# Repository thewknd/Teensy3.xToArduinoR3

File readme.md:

## Teensy 3.0 to Arduino R3 breakout

## Features
- Arduino R3 Shield compatible header
- All Teensy 3.0 pins accessible 
- Battery holder for the RTC
- micro SD card holder
- Reset/Program Button
- I2C pullup resistors
- external power supply
- battery charger circuit
- two dc dc converter (CJ1117)
- XBee (pro) compatible socket
- common nRF24L01(1) module pin header
- USB to Serial converter (FT232RL) attached to Teensy Serial3
- series resistors for all arduino R3 pins
- most parts are from Seeedstudios (new) OPLV1 (for more information: http://www.seeedstudio.com/wiki/Open_parts_library)

top

bottom

## License
Except where otherwise noted, this work is licensed under 

http://creativecommons.org/licenses/by-sa/3.0/

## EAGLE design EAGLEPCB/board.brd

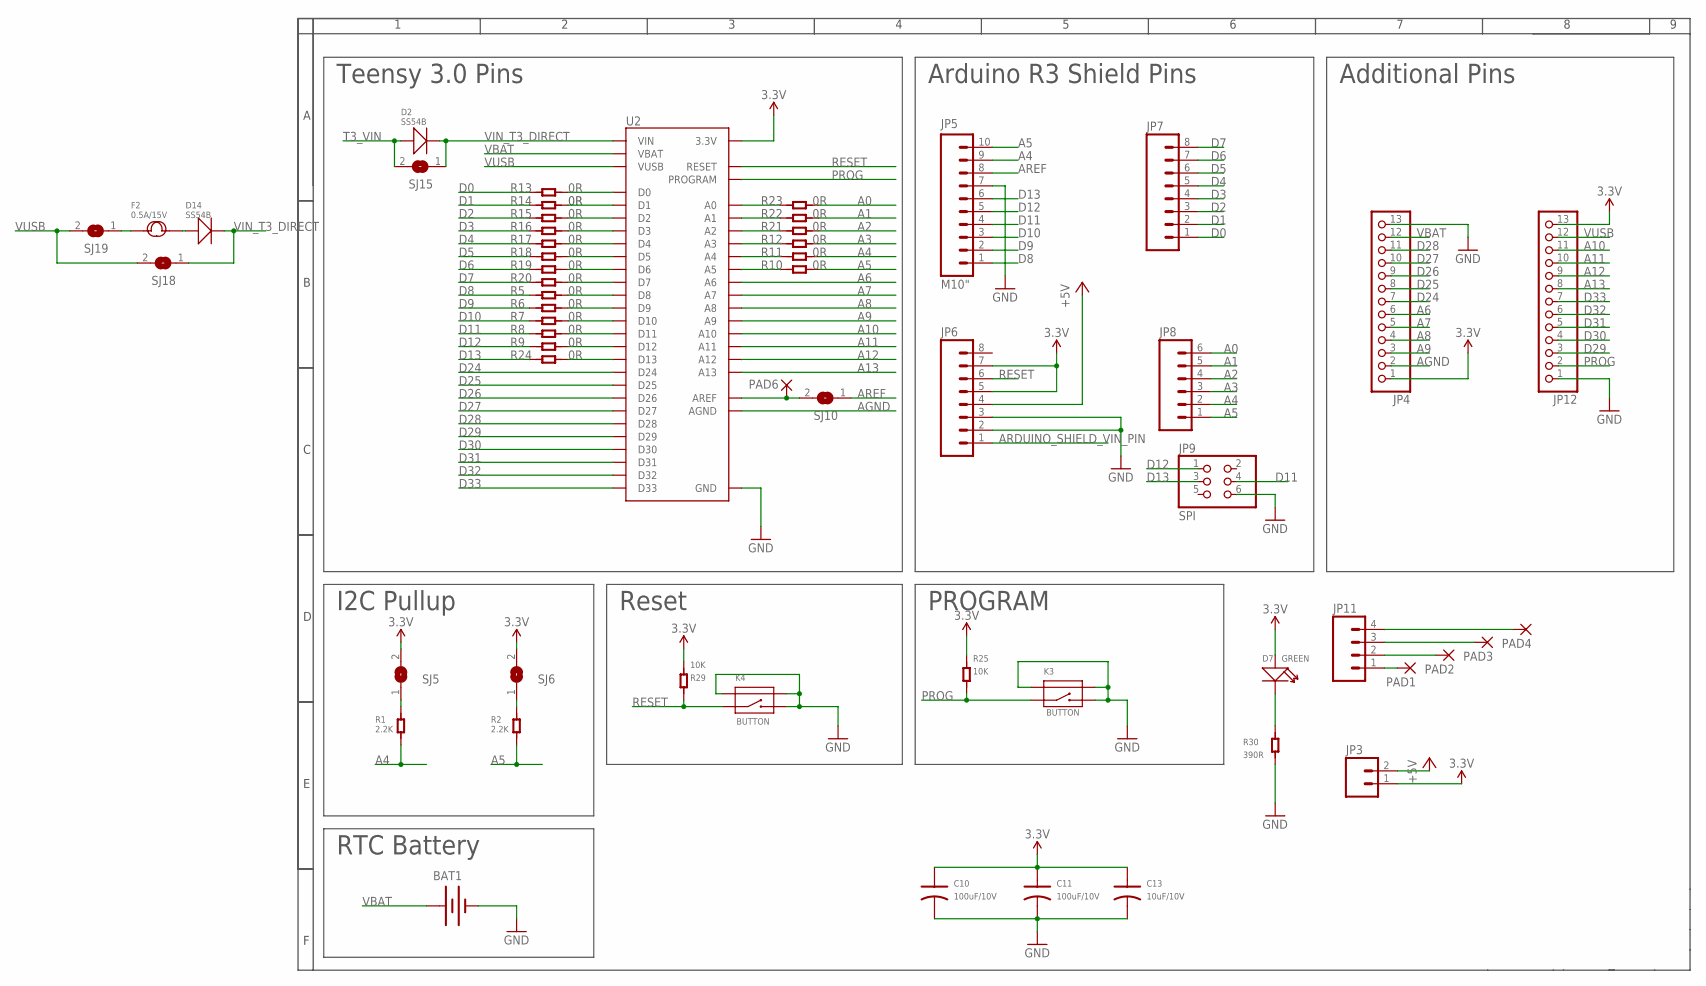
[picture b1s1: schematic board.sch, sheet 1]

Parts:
BAT1: BATTERY12MM; BATTCON_12MM
C10, C11: 100uF/10V; AVX-C
C13: 10uF/10V; AVX-B
D2, D14: SS54B; SMB
D7: GREEN; LED0603
F2: 0.5A/15V; F1812
JP3: M02PTH; 1X02
JP4, JP12: PINHD-1X13_BIG; 1X13-BIG
JP5: M10"; 1X10
JP6, JP7: M081X08; 1X08
JP8: M06SIP; 1X06
JP9: SPI; 2X03
JP11: M04PTH; 1X04
K3, K4: BUTTON; 4P-SMD-7.0X3.5X3.5H-90D
PAD1, PAD2, PAD3, PAD4: WIREPADSMD1,27-254; SMD1,27-2,54
PAD6: AREF; SMD1,27-2,54
R1, R2: 2.2K; R0603
R5, R6, R7, R8, R9, R10, R11, R12, R13, R14, R15, R16, R17, R18, R19, R20, R21, R22, R23, R24: 0R; R0603
R25, R29: 10K; R0603
R30: 390R; R0603
SJ5, SJ6, SJ10, SJ15, SJ18, SJ19: JUMPER_2WLARGE; JUMPER_LARGE_2WAY
U2: TEENSY3.0_ALLPINSSILK; TEENSY3.0_ALLPINS/SILK

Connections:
3.3V: C10.+ (1), C11.+ (1), C13.+ (1), D7.+, JP3.1, JP4.1, JP6.5, JP6.7, JP12.13, R25.2, R29.2, SJ5.2, SJ6.2, U2.3V3_A (3.3V), U2.3V3_B (3.3V), U2.3V3_C (3.3V); also elsewhere on the board
+5V: JP3.2, JP6.4; also elsewhere on the board
A0: JP8.6, R23.1
A1: JP8.5, R22.1
A2: JP8.4, R21.1
A3: JP8.3, R12.1
A4: JP5.9, JP8.2, R1.1, R11.1
A5: JP5.10, JP8.1, R2.1, R10.1
A6: JP4.6, U2.A6
A7: JP4.5, U2.A7
A8: JP4.4, U2.A8
A9: JP4.3, U2.A9
A10: JP12.11, U2.A10
A11: JP12.10, U2.A11
A12: JP12.9, U2.A12
A13: JP12.8, U2.A13
AGND: JP4.2, U2.AGND
ARDUINO_SHIELD_VIN_PIN: JP6.1; also elsewhere on the board
AREF: JP5.8, SJ10.1
D0: JP7.1, R13.2; also elsewhere on the board
D1: JP7.2, R14.2; also elsewhere on the board
D2: JP7.3, R15.2; also elsewhere on the board
D3: JP7.4, R16.2
D4: JP7.5, R17.2; also elsewhere on the board
D5: JP7.6, R18.2
D6: JP7.7, R19.2; also elsewhere on the board
D7: JP7.8, R20.2; also elsewhere on the board
D8: JP5.1, R5.2; also elsewhere on the board
D9: JP5.2, R6.2; also elsewhere on the board
D10: JP5.3, R7.2; also elsewhere on the board
D11: JP5.4, JP9.4, R8.2; also elsewhere on the board
D12: JP5.5, JP9.1, R9.2; also elsewhere on the board
D13: JP5.6, JP9.3, R24.2; also elsewhere on the board
D24: JP4.7, U2.D24; also elsewhere on the board
D25: JP4.8, U2.D25; also elsewhere on the board
D26: JP4.9, U2.D26
D27: JP4.10, U2.D27
D28: JP4.11, U2.D28
D29: JP12.3, U2.D29
D30: JP12.4, U2.D30
D31: JP12.5, U2.D31
D32: JP12.6, U2.D32
D33: JP12.7, U2.D33
DIRECT_AREF: PAD6.1, SJ10.2, U2.AREF
GND: BAT1.GND (-), C10.- (2), C11.- (2), C13.- (2), JP4.13, JP5.7, JP6.2, JP6.3, JP9.6, JP12.1, K3.2, K3.S1, K3.S2, K4.2, K4.S1, K4.S2, R30.1, U2.GND_A (GND), U2.GND_B (GND), U2.GND_C (GND); also elsewhere on the board
unnamed: R13.1, U2.D0
unnamed: R14.1, U2.D1
unnamed: R15.1, U2.D2
unnamed: R16.1, U2.D3
unnamed: R17.1, U2.D4
unnamed: R10.2, U2.A5
unnamed: R11.2, U2.A4
unnamed: R12.2, U2.A3
unnamed: R18.1, U2.D5
unnamed: R19.1, U2.D6
unnamed: R20.1, U2.D7
unnamed: R5.1, U2.D8
unnamed: R6.1, U2.D9
unnamed: R7.1, U2.D10
unnamed: R8.1, U2.D11
unnamed: R9.1, U2.D12
unnamed: R21.2, U2.A2
unnamed: R22.2, U2.A1
unnamed: R23.2, U2.A0
unnamed: R24.1, U2.D13
unnamed: R1.2, SJ5.1
unnamed: R2.2, SJ6.1
unnamed: D7.-, R30.2
unnamed: JP11.1, PAD1.1
unnamed: JP11.2, PAD2.1
unnamed: JP11.3, PAD3.1
unnamed: JP11.4, PAD4.1
unnamed: D14.+, F2.2
unnamed: F2.1, SJ19.1
PROG: JP12.2, K3.1, R25.1, U2.PROG (PROGRAM)
RESET: JP6.6, K4.1, R29.1, U2.RESET; also elsewhere on the board
T3_VIN: D2.+, SJ15.2; also elsewhere on the board
VBAT: BAT1.PWR@1 (+), JP4.12, U2.VBAT
VIN_T3_DIRECT: D2.-, D14.-, SJ15.1, SJ18.1, U2.VIN
VUSB: JP12.12, SJ18.2, SJ19.2, U2.VUSB; also elsewhere on the board

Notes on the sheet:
Teensy 3.0 Pins
Arduino R3 Shield Pins
I2C Pullup
Reset
Additional Pins
PROGRAM
RTC Battery

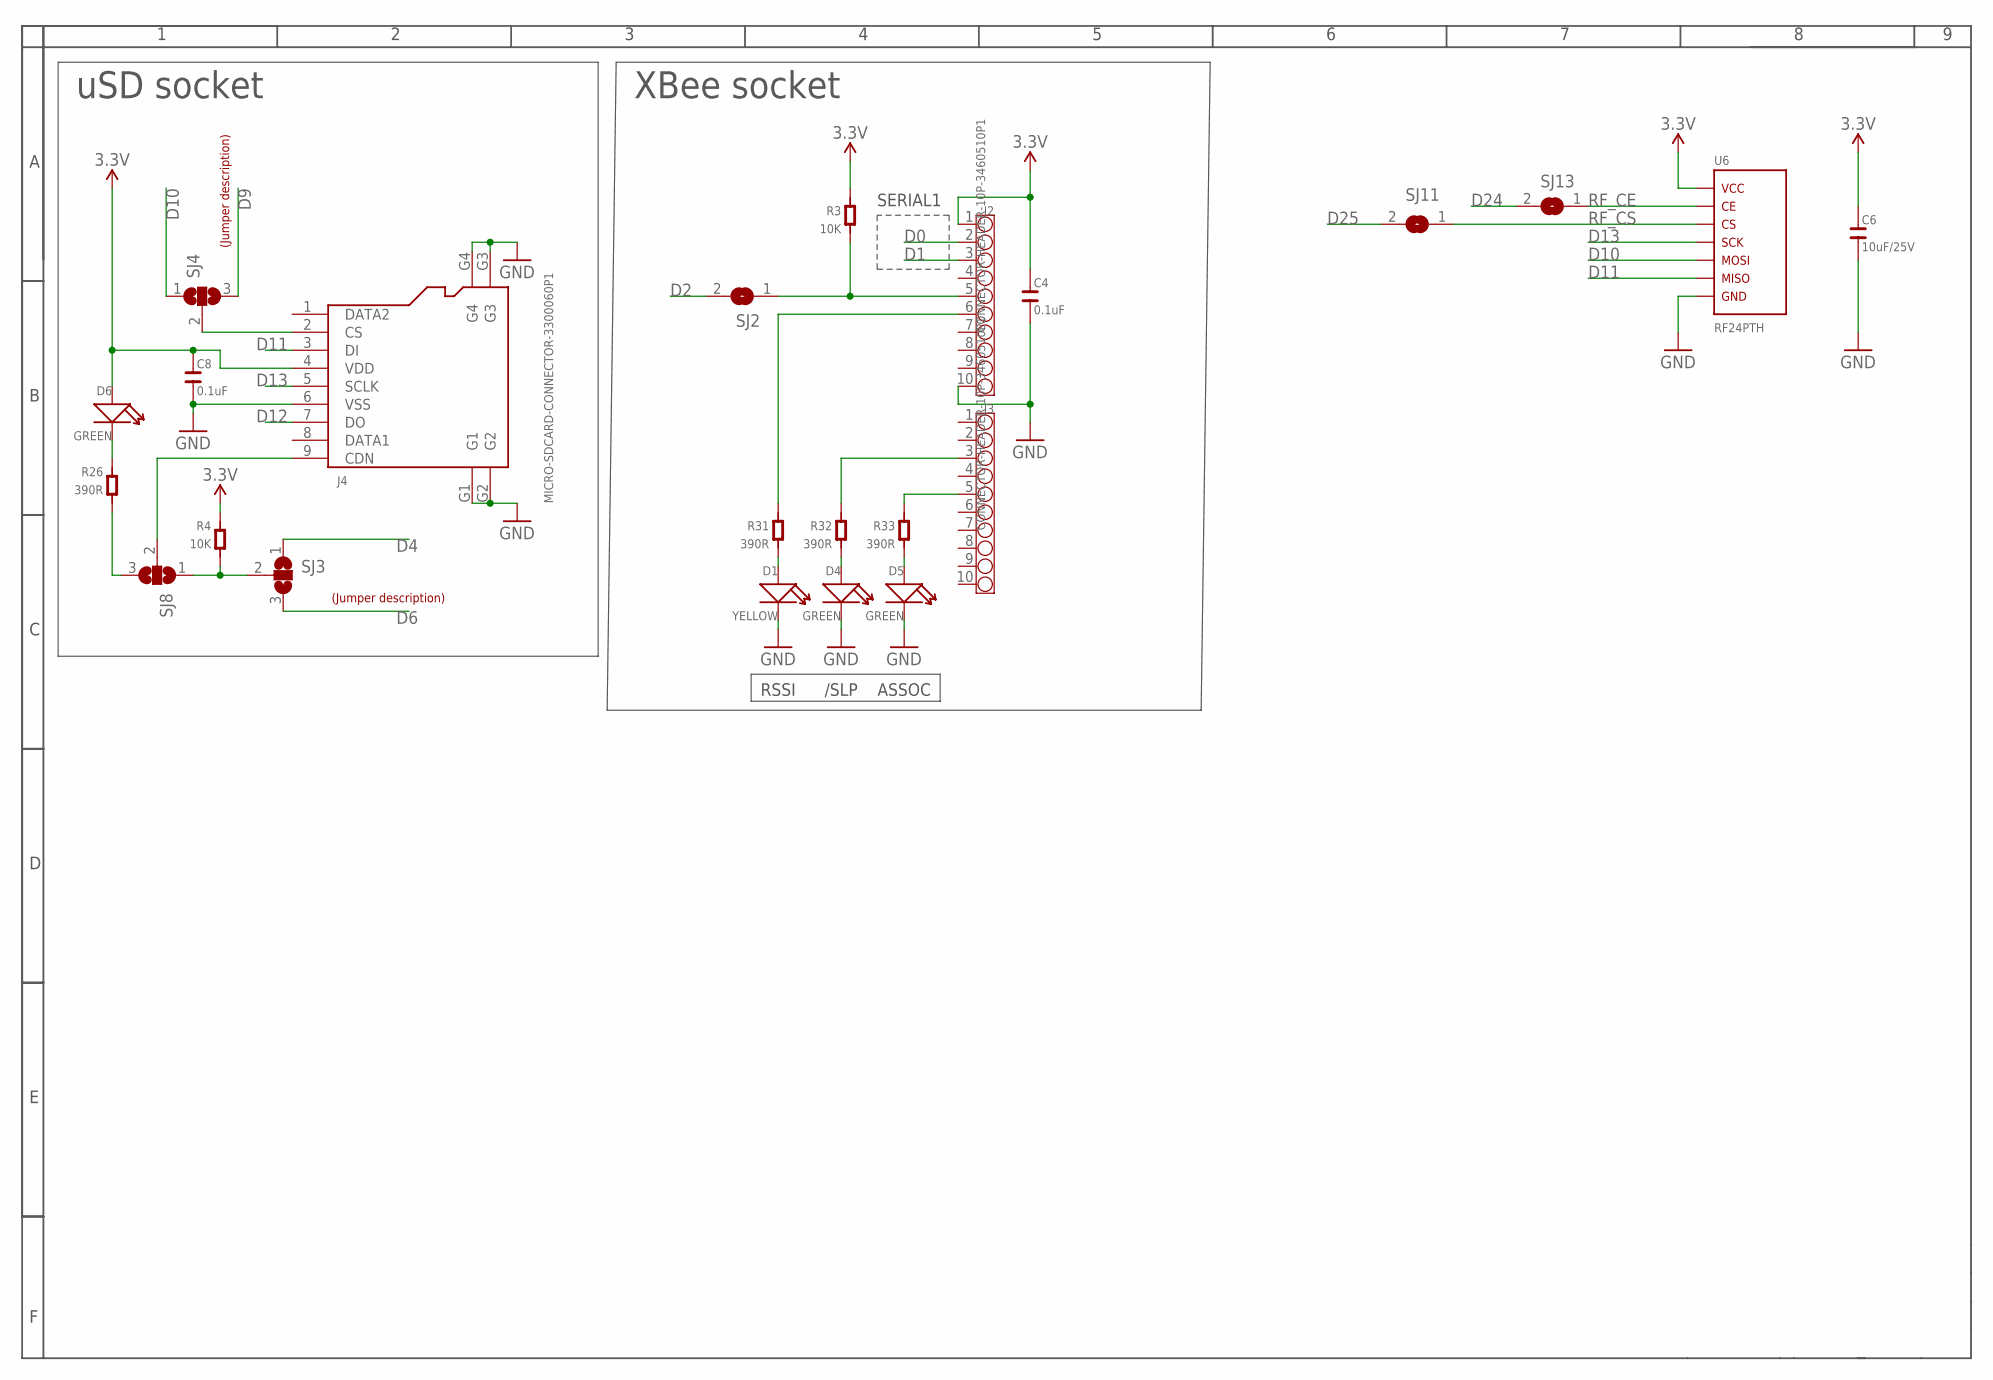
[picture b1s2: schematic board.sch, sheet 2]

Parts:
C4, C8: 0.1uF; C0603
C6: 10uF/25V; C0805
D1: YELLOW; LED0603
D4, D5, D6: GREEN; LED0603
J2, J3: CONNECTOR-HEADER-10P-3460510P1; 1X10P-2.0-4.3-BLUE-FEMALE
J4: MICRO-SDCARD-CONNECTOR-3300060P1; 9P-SMD-W-RING
R3, R4: 10K; R0603
R26, R31, R32, R33: 390R; R0603
SJ2, SJ11, SJ13: JUMPER_2WSMALL; JUMPER_SMALL_2WAY
SJ3, SJ4, SJ8: SJ2W; SJ_2
U6: RF24PTH; RF24
U$1, U$2: LABEL_JUMPER_1X3; JUMP3_DESC

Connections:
3.3V: C4.2, C6.2, C8.2, D6.+, J2.1, J4.4 (VDD), R3.2, R4.1, U6.VCC; also elsewhere on the board
D0: J2.2; also elsewhere on the board
D1: J2.3; also elsewhere on the board
D2: SJ2.2; also elsewhere on the board
D4: SJ3.1; also elsewhere on the board
D6: SJ3.3; also elsewhere on the board
D9: SJ4.3; also elsewhere on the board
D10: SJ4.1, U6.MOSI; also elsewhere on the board
D11: J4.3 (DI), U6.MISO; also elsewhere on the board
D12: J4.7 (DO); also elsewhere on the board
D13: J4.5 (SCLK), U6.SCK; also elsewhere on the board
D24: SJ13.2; also elsewhere on the board
D25: SJ11.2; also elsewhere on the board
DFGDFG: J2.5, R3.1, SJ2.1
ESDASGGGG: R4.2, SJ3.2, SJ8.1
GND: C4.1, C6.1, C8.1, D1.-, D4.-, D5.-, J2.10, J4.6 (VSS), J4.G1, J4.G2, J4.G3, J4.G4, U6.GND; also elsewhere on the board
unnamed: J3.5, R33.2
unnamed: D1.+, R31.1
unnamed: D4.+, R32.1
unnamed: J3.3, R32.2
unnamed: D5.+, R33.1
unnamed: R26.1, SJ8.3
unnamed: J2.6, R31.2
unnamed: D6.-, R26.2
unnamed: J4.9 (CDN), SJ8.2
unnamed: J4.2 (CS), SJ4.2
RF_CE: SJ13.1, U6.CE
RF_CS: SJ11.1, U6.CS

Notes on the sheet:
uSD socket
XBee socket
SERIAL1
ASSOC
/SLP
RSSI

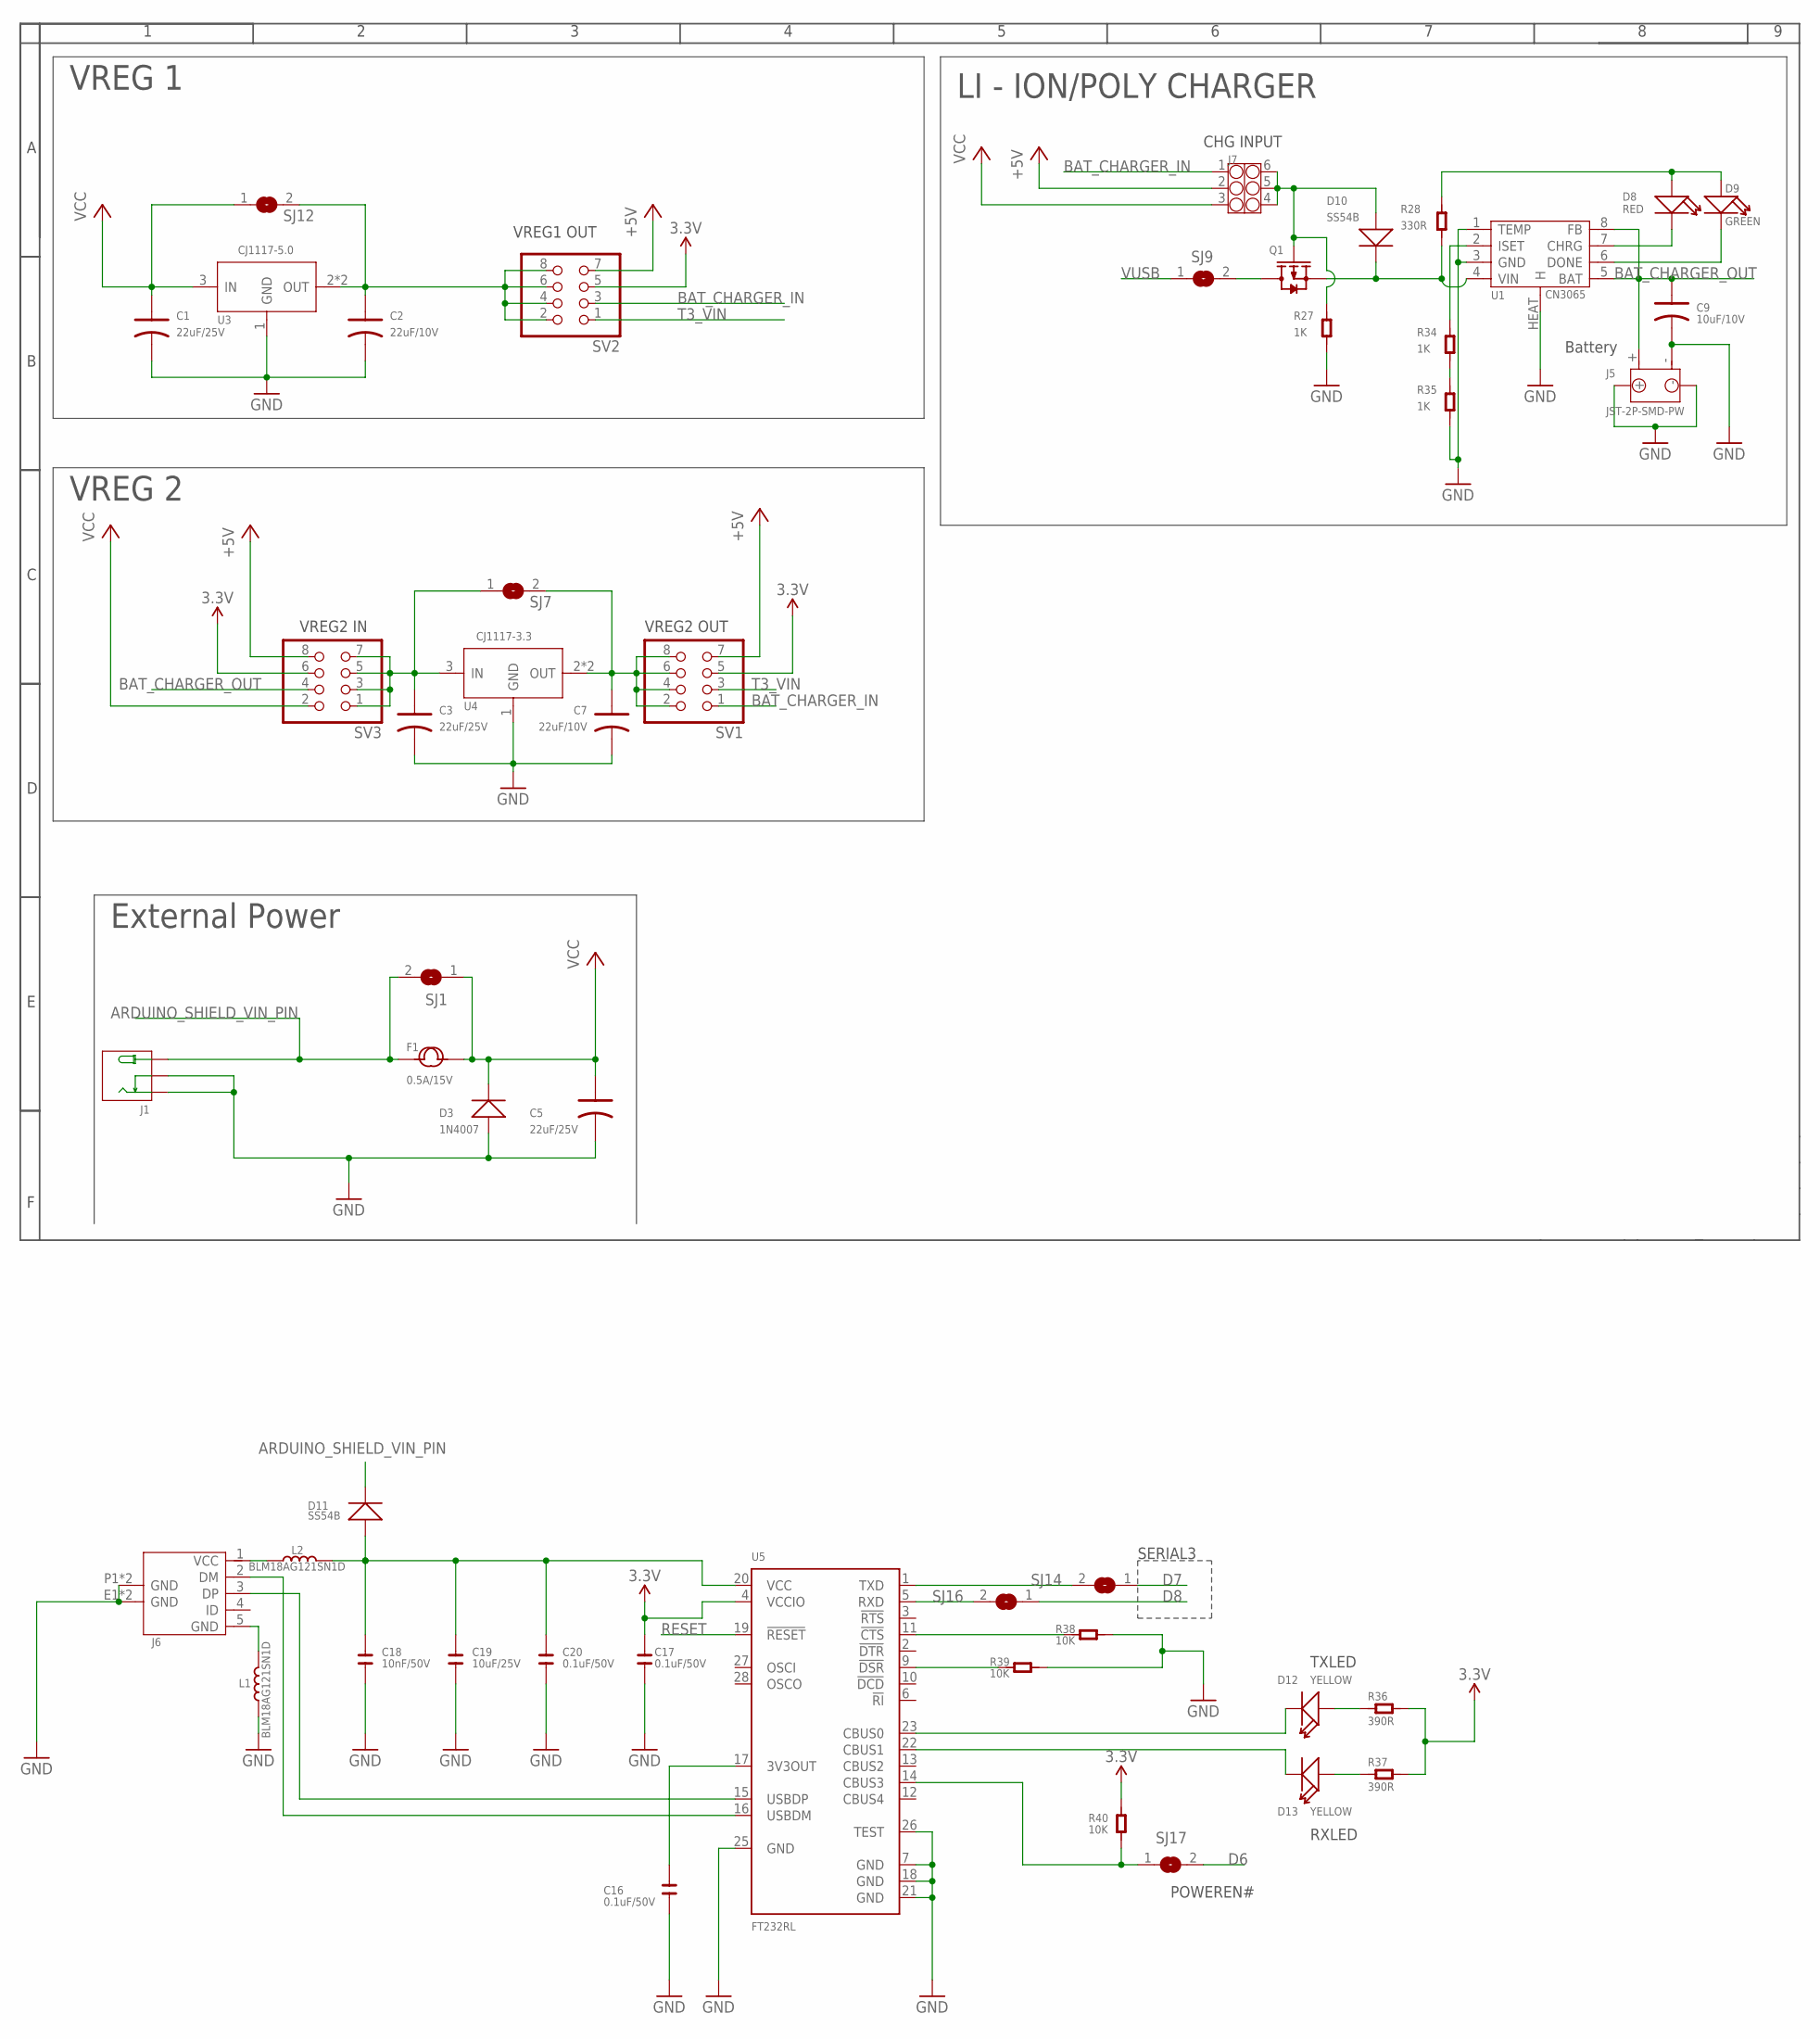
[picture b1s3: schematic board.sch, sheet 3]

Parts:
C1, C3: 22uF/25V; AVX-C; MPN TAJC226K025RNJ
C2, C7: 22uF/10V; AVX-B
C5: 22uF/25V; AVX-C
C9: 10uF/10V; AVX-A
C16, C17, C20: 0.1uF/50V; C0603
C18: 10nF/50V; C0603
C19: 10uF/25V; C0805
D3: 1N4007; DO-214AC
D8: RED; LED0603
D9: GREEN; LED0603
D10, D11: SS54B; SMB
D12, D13: YELLOW; LED0603
F1: 0.5A/15V; F1812
J1: JACK-DC-3P-3410020P1; PW-3P-2.1
J5: JST-2P-SMD-PW; 2P-SMD-2.0-90D
J6: MICRO-USB-5P-3400150P1; B-SMD-5P
J7: CONNECTOR-HEADER-2X3P-3460180P1; 2X3P-2.54-2.54-11.6-3.0-BLACK-MALE
L1, L2: BLM18AG121SN1D; L0603
Q1: MOSFET-P-0440210P1; SOT23
R27, R34, R35: 1K; R0603
R28: 330R; R0603
R36, R37: 390R; R0603
R38, R39, R40: 10K; R0603
SJ1, SJ7, SJ9, SJ12, SJ14, SJ16, SJ17: JUMPER_2WLARGE; JUMPER_LARGE_2WAY
SV1, SV2, SV3: PINHD-2X4_2.54; 2X04
U1: CN3065; DFN8
U3: CJ1117-5.0; SOT223
U4: CJ1117-3.3; SOT223
U5: FT232RL; SSOP28

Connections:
3.3V: C17.1, R36.2, R37.2, R40.2, SV1.5, SV2.5, SV3.6, U5.4 (VCCIO); also elsewhere on the board
+5V: J7.2, SV1.7, SV2.7, SV3.8; also elsewhere on the board
ARDUINO_SHIELD_VIN_PIN: D11.-, F1.1, J1.+, SJ1.2; also elsewhere on the board
BAT_CHARGER_IN: J7.1, SV1.1, SV2.3
BAT_CHARGER_OUT: C9.+ (1), J5.+, SV3.4, U1.5 (BAT), U1.8 (FB)
D6: SJ17.2; also elsewhere on the board
D7: SJ14.1; also elsewhere on the board
D8: SJ16.1; also elsewhere on the board
GND: C1.- (2), C2.- (2), C3.- (2), C5.- (2), C7.- (2), C9.- (2), C16.2, C17.2, C18.2, C19.2, C20.2, D3.1 (+), J1.-1 (-), J1.-2 (CDN), J5.3, J5.4, J5.-, J6.E1 (GND), J6.E2 (GND), J6.P1 (GND), J6.P2 (GND), L1.1, R27.1, R35.1, R38.2, R39.2, U1.1 (TEMP), U1.3 (GND), U1.HEAT (H), U3.1 (GND), U4.1 (GND), U5.7 (GND), U5.18 (GND), U5.21 (GND), U5.25 (GND), U5.26 (TEST); also elsewhere on the board
unnamed: C3.+ (1), SJ7.1, SV3.1, SV3.3, SV3.5, SV3.7, U4.3 (IN)
unnamed: C7.+ (1), SJ7.2, SV1.2, SV1.4, SV1.6, SV1.8, U4.2 (OUT), U4.TER (OUT)
unnamed: D10.-, Q1.2 (S), R28.1, U1.4 (VIN)
unnamed: C18.1, C19.1, C20.1, D11.+, L2.2, U5.20 (VCC)
unnamed: D8.-, U1.7 (CHRG)
unnamed: D9.-, U1.6 (DONE)
unnamed: D8.+, D9.+, R28.2
unnamed: R34.2, U1.2 (ISET)
unnamed: Q1.3 (D), SJ9.2
unnamed: J6.2 (DM), U5.16 (USBDM)
unnamed: J6.3 (DP), U5.15 (USBDP)
unnamed: R38.1, U5.11 (!CTS)
unnamed: R39.1, U5.9 (!DSR)
unnamed: SJ14.2, U5.1 (TXD)
unnamed: C2.+ (1), SJ12.2, SV2.2, SV2.4, SV2.6, SV2.8, U3.2 (OUT), U3.TER (OUT)
unnamed: SJ16.2, U5.5 (RXD)
unnamed: D12.-, U5.23 (CBUS0)
unnamed: R40.1, SJ17.1, U5.14 (CBUS3)
unnamed: D13.-, U5.22 (CBUS1)
unnamed: R34.1, R35.2
unnamed: C16.1, U5.17 (3V3OUT)
unnamed: D12.+, R36.1
unnamed: D13.+, R37.1
unnamed: J6.5 (GND), L1.2
unnamed: J6.1 (VCC), L2.1
NET45456: D10.+, J7.4, J7.5, J7.6, Q1.1 (G), R27.2
RESET: U5.19 (!RESET); also elsewhere on the board
T3_VIN: SV1.3, SV2.1; also elsewhere on the board
VCC: C1.+ (1), C5.+ (1), D3.2 (-), F1.2, J7.3, SJ1.1, SJ12.1, SV3.2, U3.3 (IN)
VUSB: SJ9.1; also elsewhere on the board

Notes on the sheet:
External Power
VREG 2
VREG 1
LI - ION/POLY CHARGER
SERIAL3
TXLED
RXLED
VREG1 OUT
VREG2 OUT
VREG2 IN
CHG INPUT
Battery
POWEREN#

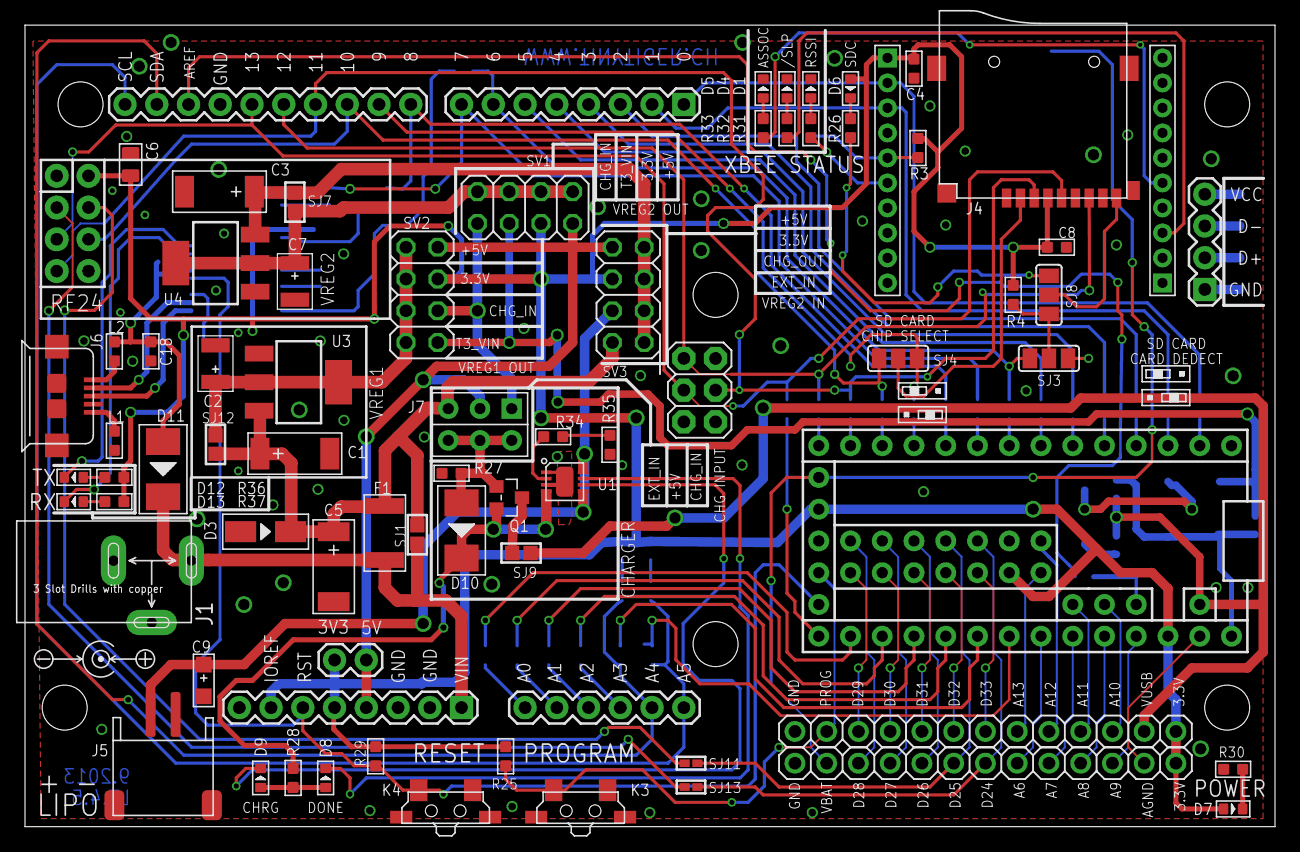
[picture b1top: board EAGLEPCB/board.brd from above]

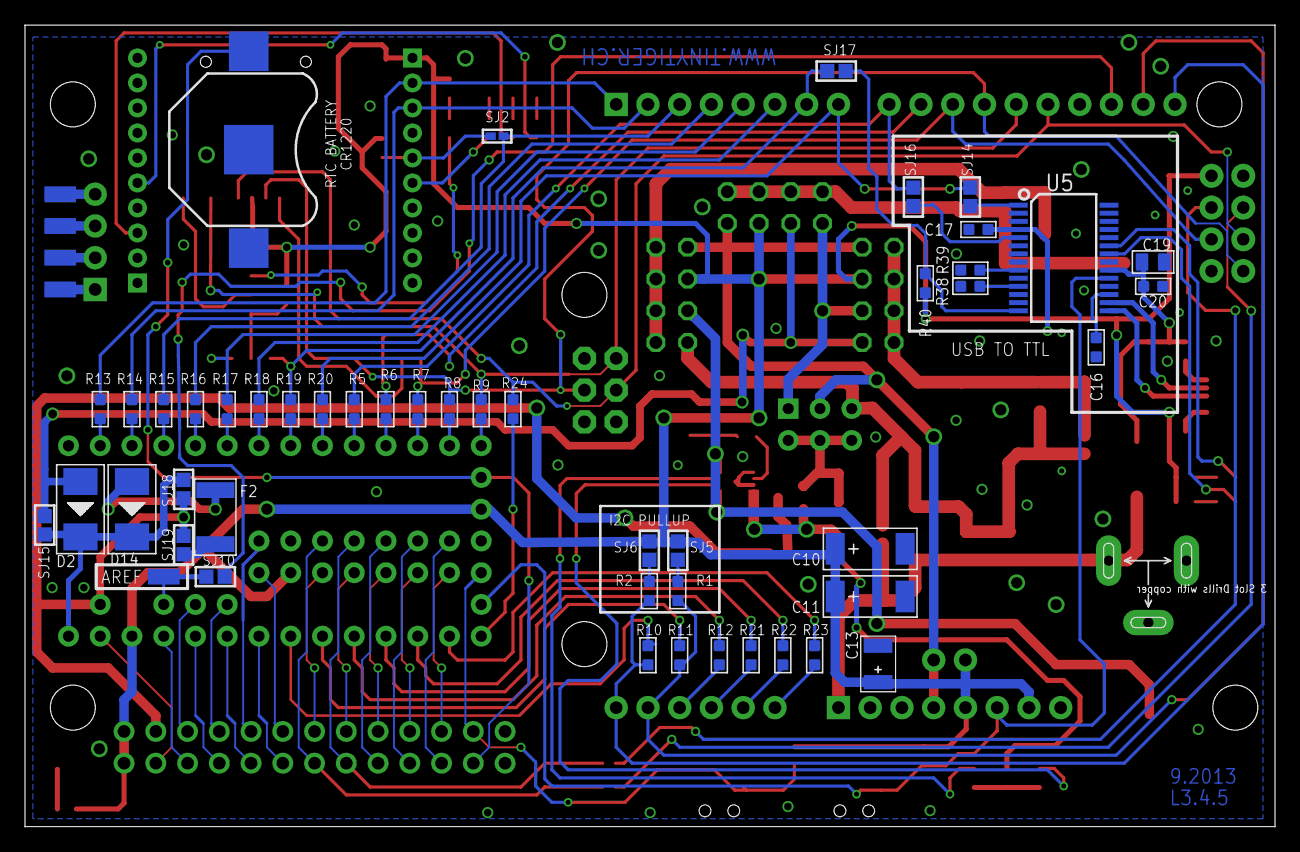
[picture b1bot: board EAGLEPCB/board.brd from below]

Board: 2 copper layers, 100.0 x 64.1 mm, 130 parts (52 on the bottom side), 123 nets.

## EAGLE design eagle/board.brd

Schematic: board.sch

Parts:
BAT1: BATTERY12MM; BATTCON_12MM
C1, C2, C3: CAPACITOR_POL-3216-POL; 3216C-POL
C4, C5, C6, C7, C8, C11, C12, C13, C16, C17: CAPACITOR-0805; 0805C
C9: CPOL-EUD; PANASONIC_D
C10: CPOL-EU085CS-1AR; 085CS_1AR
CN1, CN3: JST_2PIN-THM-RA; JST-PH-2-THM-RA
CN2: DCBARRELPTH; DCJACK_2MM_PTH
D1, D2: DIODESMA-KIT; SMA-DIODE-KIT
F1, F2: FUSE1812; 1812STD
IC1: 78XX compatible; TO220V
IC2, IC3, IC4, IC5: 24AA1025SM; SOIC-8
IC6: LTC2862; SO08
IC7: TMP102; SOT563
IC8: MS5803-01BA; MS5803
IC9: MCP73871; QFN-20
JP1, JP3: M14; 1X14
JP2, JP4: PINHD-2X6; 2X06
JP5, JP17, JP18: M10"; 1X10
JP6, JP7: M081X08; 1X08
JP8: M06SIP; 1X06
JP9: SPI; 2X03
JP11: M03PTH; 1X03
JP14: PINHD-1X2; 1X02
JP15: M02PTH; 1X02
JP16: M05PTH; 1X05
P1, P2, P3, P4, P5, P6, P7, P8, P9, P10, P11, P12, P13: LED; LED0805
Q1, Q2, Q3, Q4, Q5, Q6, Q7: 2N7002; SOT23
R1, R2, R3, R5, R6, R7, R8, R9, R10, R11, R12, R13, R14, R15, R16, R17, R18, R19, R20, R21, R22, R23, R24, R25, R26, R27, R28, R29, R30, R31, R32, R33, R34, R35, R36, R37, R38, R39, R40, R41, R42, R43, R44, R45, R46, R47, R48, R49, R50, R51, R52, R53, R54, R55, R56, R57, R58, R59, R60, R61, R62, R63, R64, R65, R66: RESISTOR; R0805
R4: R4; R0805
S1: TAC_SWITCHPTH; TACTILE-PTH
SJ1, SJ2, SJ3, SJ4, SJ5, SJ6, SJ7, SJ8, SJ9, SJ10, SJ11, SJ12, SJ13, SJ14, SJ15, SJ16, SJ17, SJ18, SJ19, SJ20, SJ25, SJ26, SJ27, SJ28, SJ29, SJ30: SOLDERJUMPERNO; SJ_2S-NO
SJ21, SJ22, SJ23, SJ24: SOLDERJUMPER_2WAYT; SJ_2
U1: MICROSD
U$1: XBEE-1B2; XBEE-SILK
U$3, U$4: M24; 1X24
X1: W237-102
X2: W237-03P; W237-133
X3, X4, X5: HEADER-2X2; HEADER-PTH-2X2
X6: HEADER-2X10SLK; HEADER-PTH-2X10

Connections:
3.3V: C4.1, C5.1, C6.1, C7.1, C8.1, C11.1, C13.1, IC2.3 (A2), IC2.8 (VCC), IC3.2 (A1), IC3.3 (A2), IC3.8 (VCC), IC4.1 (A0), IC4.3 (A2), IC4.8 (VCC), IC5.1 (A0), IC5.2 (A1), IC5.3 (A2), IC5.8 (VCC), IC6.8 (VCC), IC8.3 (CSB), IC8.5 (VDD), IC8.6 (PS), JP2.3, JP2.4, JP2.5, JP2.6, JP3.12, JP6.5, JP6.7, JP16.4, R1.2, R2.2, R3.2, R4.2, R46.2, R48.2, R53.1, R54.1, R55.1, R56.1, R57.2, R58.2, R59.2, R60.2, R61.2, R62.2, R63.2, R66.2, SJ13.1, SJ21.3, SJ22.3, SJ23.3, SJ24.3, U1.4 (VDD), U$1.1 (VDD), U$4.23, X5.3, X6.1
5V: JP6.4, SJ13.2
/PG: IC9.6 (/PG), P12.C
A0: JP8.6, R23.1, U$4.13
A1: JP8.5, R22.1, U$4.14
A2: JP8.4, R21.1, U$4.15
A3: JP8.3, R12.1, U$4.16
A4: IC2.5 (SDA), IC3.5 (SDA), IC4.5 (SDA), IC5.5 (SDA), IC7.6 (SDA), IC8.7 (SDI/SDA), JP5.9, JP8.2, R1.1, R11.1, U$4.17
A5: IC2.6 (SCL), IC3.6 (SCL), IC4.6 (SCL), IC5.6 (SCL), IC7.1 (SCL), IC8.1 (SCLK), JP5.10, JP8.1, R2.1, R10.1, U$4.18
A6: R38.1, SJ8.2, SJ12.2, U$4.19
A7: R37.1, SJ7.2, SJ11.2, U$4.20
A8: R36.1, U$4.21
A9: R35.1, U$4.22
A10: R42.1, U$4.2
A11: R41.1, U$4.3
A12: R40.1, U$4.4
A13: R39.1, U$4.5
AGND: JP3.13, U$4.24
AREF: JP18.6, SJ15.2, U$4.7
BAT_CHARGER: C17.1, IC9.18 (IN1), IC9.19 (IN1), X4.1, X4.3
CE: IC9.17 (CE), SJ24.2
D0: JP7.1, R13.1, SJ25.1, SJ29.1, U$3.24
D1: JP7.2, R14.1, SJ20.2, SJ30.1, U$3.23
D2: JP7.3, R15.1, U$3.22
D3: JP7.4, R16.1, U$3.21
D4: JP7.5, R17.1, SJ3.2, U$3.20
D5: JP7.6, R18.1, SJ4.2, U$3.19
D6: JP7.7, R19.1, SJ16.1, SJ17.1, U$3.18
D7: IC6.1 (RO), JP7.8, R20.1, SJ26.2, U$3.17
D8: IC6.4 (DI), JP5.1, R5.1, SJ27.1, U$3.16
D9: JP5.2, R6.1, SJ5.2, SJ9.2, SJ19.1, U$3.15
D10: JP5.3, R7.1, SJ6.2, SJ10.2, SJ18.1, U$3.14
D11: JP4.5, JP4.6, JP5.4, JP9.4, R8.1, U1.3 (DATA_IN), U$3.13
D12: JP2.11, JP2.12, JP5.5, JP9.1, R9.1, U1.7 (DATA_OUT), U$3.12
D13: JP4.7, JP4.8, JP5.6, JP9.3, R24.1, U1.5 (SCLK), U$4.12
D24: R25.1, U$3.11
D25: R26.1, U$3.10
D26: R27.1, U$3.9
D27: R28.1, U$3.8
D28: R29.1, U$3.7
D29: R30.1, U$3.6
D30: R31.1, U$3.5
D31: R32.1, U$3.4
D32: R33.1, U$3.3
D33: R34.1, U$3.2
DIO0: U$1.20 (DIO0), X6.2
DIO1: U$1.19 (DIO1), X6.4
DIO2: U$1.18 (DIO2), X6.6
DIO3: U$1.17 (DIO3), X6.8
DIO4: U$1.11 (DIO4), X6.20
DIO5: U$1.15 (DIO5), X6.12
DIO9: U$1.13 (DIO9), X6.16
DIO11: U$1.7 (DIO11), X6.13
DIO12: U$1.4 (DIO12), X6.7
EXT_POWER: CN1.1 (2), CN2.PWR, F2.+, SJ1.2, X1.1
EXT_RESET: JP6.6, JP11.2, R3.1, S1.3, S1.4
GND: BAT1.GND (-), C1.-, C2.-, C3.-, C4.2, C5.2, C6.2, C7.2, C8.2, C9.-, C10.-, C11.2, C12.2, C13.2, C16.2, C17.2, CN1.2 (1), CN2.GND, CN2.GNDBREAK, CN3.2 (1), D1.A, IC1.2 (GND), IC2.1 (A0), IC2.2 (A1), IC2.4 (GND), IC2.7 (WP), IC3.1 (A0), IC3.4 (GND), IC3.7 (WP), IC4.2 (A1), IC4.4 (GND), IC4.7 (WP), IC5.4 (GND), IC5.7 (WP), IC6.5 (GND), IC7.2 (GND), IC7.4 (ADD0), IC8.2 (GND), IC9.10 (GND1), IC9.11 (GND1), IC9.21 (GND1), IC9.22 (GND1), IC9.P$1 (GND1), IC9.P$2 (GND1), IC9.P$3 (GND1), IC9.P$4 (GND1), JP1.14, JP2.1, JP2.2, JP4.1, JP4.2, JP4.3, JP4.4, JP5.7, JP6.2, JP6.3, JP9.6, JP16.3, JP18.9, P8.C, P9.C, P13.C, Q1.2 (S), Q2.2 (S), Q3.2 (S), Q4.2 (S), Q5.2 (S), Q6.2 (S), Q7.2 (S), R44.2, R45.1, R49.2, R50.2, R51.2, R52.2, S1.1, S1.2, SJ21.1, SJ22.1, SJ23.1, SJ24.1, U1.6 (VSS), U1.MT1 (GND), U1.MT2 (GND1), U$1.10 (GND), U$3.25, U$4.10, X1.2, X2.1, X6.19
unnamed: D1.C, F2.-, SJ1.1, X3.2, X3.4
unnamed: F1.-, JP15.2, SJ14.1
unnamed: C1.+, D2.C, IC1.1 (VI), SJ2.2, X3.1
unnamed: JP1.5, R5.2
unnamed: JP1.4, R6.2
unnamed: JP1.3, R7.2
unnamed: JP1.2, R8.2
unnamed: JP1.1, R9.2
unnamed: JP3.7, R10.2
unnamed: JP3.6, R11.2
unnamed: JP3.5, R12.2
unnamed: JP1.13, R13.2
unnamed: JP1.12, R14.2
unnamed: JP1.11, R15.2
unnamed: JP1.10, R16.2
unnamed: JP1.9, R17.2
unnamed: JP1.8, R18.2
unnamed: JP1.7, R19.2
unnamed: JP1.6, R20.2
unnamed: JP3.4, R21.2
unnamed: JP3.3, R22.2
unnamed: JP3.2, R23.2
unnamed: JP3.1, R24.2
unnamed: JP17.10, R25.2
unnamed: JP17.9, R26.2
unnamed: JP17.8, R27.2
unnamed: JP17.7, R28.2
unnamed: JP17.6, R29.2
unnamed: JP17.5, R30.2
unnamed: JP17.4, R31.2
unnamed: JP17.3, R32.2
unnamed: JP17.2, R33.2
unnamed: JP17.1, R34.2
unnamed: JP3.11, R35.2
unnamed: JP3.10, R36.2
unnamed: JP3.9, R37.2
unnamed: JP3.8, R38.2
unnamed: JP18.4, R39.2
unnamed: JP18.3, R40.2
unnamed: JP18.2, R41.2
unnamed: JP18.1, R42.2
unnamed: IC6.2 (RE/), JP14.2, SJ16.2
unnamed: IC6.3 (DE), JP14.1, SJ17.2, SJ28.2
unnamed: P5.C, Q5.3 (D)
unnamed: P5.A, R57.1
unnamed: P4.A, R59.1
unnamed: P3.A, R58.1
unnamed: P3.C, Q4.3 (D)
unnamed: P4.C, Q3.3 (D)
unnamed: P1.A, R61.1
unnamed: JP4.9, JP4.10, SJ9.1, SJ10.1, SJ11.1, SJ12.1
unnamed: JP4.11, JP4.12
unnamed: P2.A, R60.1
unnamed: P1.C, Q2.3 (D)
unnamed: P2.C, Q1.3 (D)
unnamed: JP2.7, JP2.8
unnamed: JP2.9, JP2.10
unnamed: P7.A, R63.1
unnamed: P6.A, R62.1
unnamed: P6.C, Q7.3 (D)
unnamed: P7.C, Q6.3 (D)
unnamed: JP5.8, SJ15.1
unnamed: Q7.1 (G), SJ18.2
unnamed: C10.+, SJ14.2
unnamed: Q6.1 (G), SJ19.2
unnamed: Q1.1 (G), SJ20.1
unnamed: Q2.1 (G), SJ25.2
unnamed: Q5.1 (G), SJ28.1
unnamed: Q3.1 (G), SJ26.1
unnamed: Q4.1 (G), SJ27.2
unnamed: P8.A, R65.1
unnamed: P9.A, R64.1
unnamed: P13.A, R66.1
unnamed: C16.1, CN3.1 (2), IC9.14 (VBAT1), IC9.15 (VBAT1), IC9.16 (VBAT1)
unnamed: R43.1, R44.1, R49.1
unnamed: IC9.5 (THERM), R43.2
unnamed: IC9.12 (PROG3), R50.1
unnamed: IC9.13 (PROG1), R51.1
unnamed: IC9.2 (VPCC), R52.1, R53.2
unnamed: C2.+, C9.+, D2.A, IC1.3 (VO), SJ2.1, X5.2, X5.4
unnamed: X4.2, X5.1
unnamed: P12.A, R54.2
unnamed: P11.A, R55.2
unnamed: P10.A, R56.2
NIC: R4.1, SJ3.1, SJ4.1, U1.CD1 (CARD_DETECT)
PROG: JP11.3, JP16.2, JP18.5, U$4.6
PROG2: IC9.4 (PROG2), SJ22.2
QW: SJ5.1, SJ6.1, SJ7.1, SJ8.1, U1.2 (CS)
RESET: JP11.1, JP16.1, JP18.7, U$4.8
RS485A: IC6.6 (A), R45.2, R47.1, X2.2
RS485B: IC6.7 (B), R46.1, R47.2, X2.3
SEL: IC9.3 (SEL), SJ21.2
STAT1: IC9.8 (STAT1/LBO), P10.C
STAT2: IC9.7 (STAT2), P11.C
TE: IC9.9 (/TE), SJ23.2
VBAT: BAT1.PWR@1 (+), JP16.5, JP18.10, U$4.11
VCC: C12.1, IC7.5 (VCC), R48.1
VIN: IC9.1 (OUT1), IC9.20 (OUT1), JP3.14, JP6.1, JP15.1, U$4.25, X3.3
VUSB: C3.+, F1.+, JP18.8, U$4.9, X4.4
XBEE_CTS: U$1.12 (CTS), X6.18
XBEE_DIN: SJ30.2, U$1.3 (DIN), X6.5
XBEE_DOUT: SJ29.2, U$1.2 (DOUT), X6.3
XBEE_DTR: U$1.9 (DTR), X6.17
XBEE_RES1: U$1.8 (RES), X6.15
XBEE_RSSI: R65.2, U$1.6 (RSSI), X6.11
XBEE_RST: U$1.5 (RESET), X6.9
XBEE_RTS: R64.2, U$1.16 (RTS), X6.10
XBEE_VREF: U$1.14 (RES), X6.14

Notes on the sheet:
Teensy 3.0 Pins
Arduino R3 Shield Pins
I2C Pullup
External Power
Reset
RTC Battery
5V Supply
Teensy 3.0 to Arduino R3 adapter This work is licensed under a Creative Commons Attribution-ShareAlike 3.0 Unported License. http://creativecommons.org/licenses/by-sa/3.0/ (c) 2012 Jonas Niggli (thewknd)
MISC
I2C EEPROM
uSD socket
RS485B
RS485A
Serial3
Serial1
RS485
XBee
WIZ820io
TMP102
I2C address: 1001000
I2C address: 1110110
MS5803-01BA
Serial2 LED
Serial1 LED
Serial3 LED
MCP73871
POWER LED

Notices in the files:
parts and their libraries:
SparkFun-Connectors: Licensing: CC v3.0 Share-Alike You are welcome to use this library for commercial purposes.
